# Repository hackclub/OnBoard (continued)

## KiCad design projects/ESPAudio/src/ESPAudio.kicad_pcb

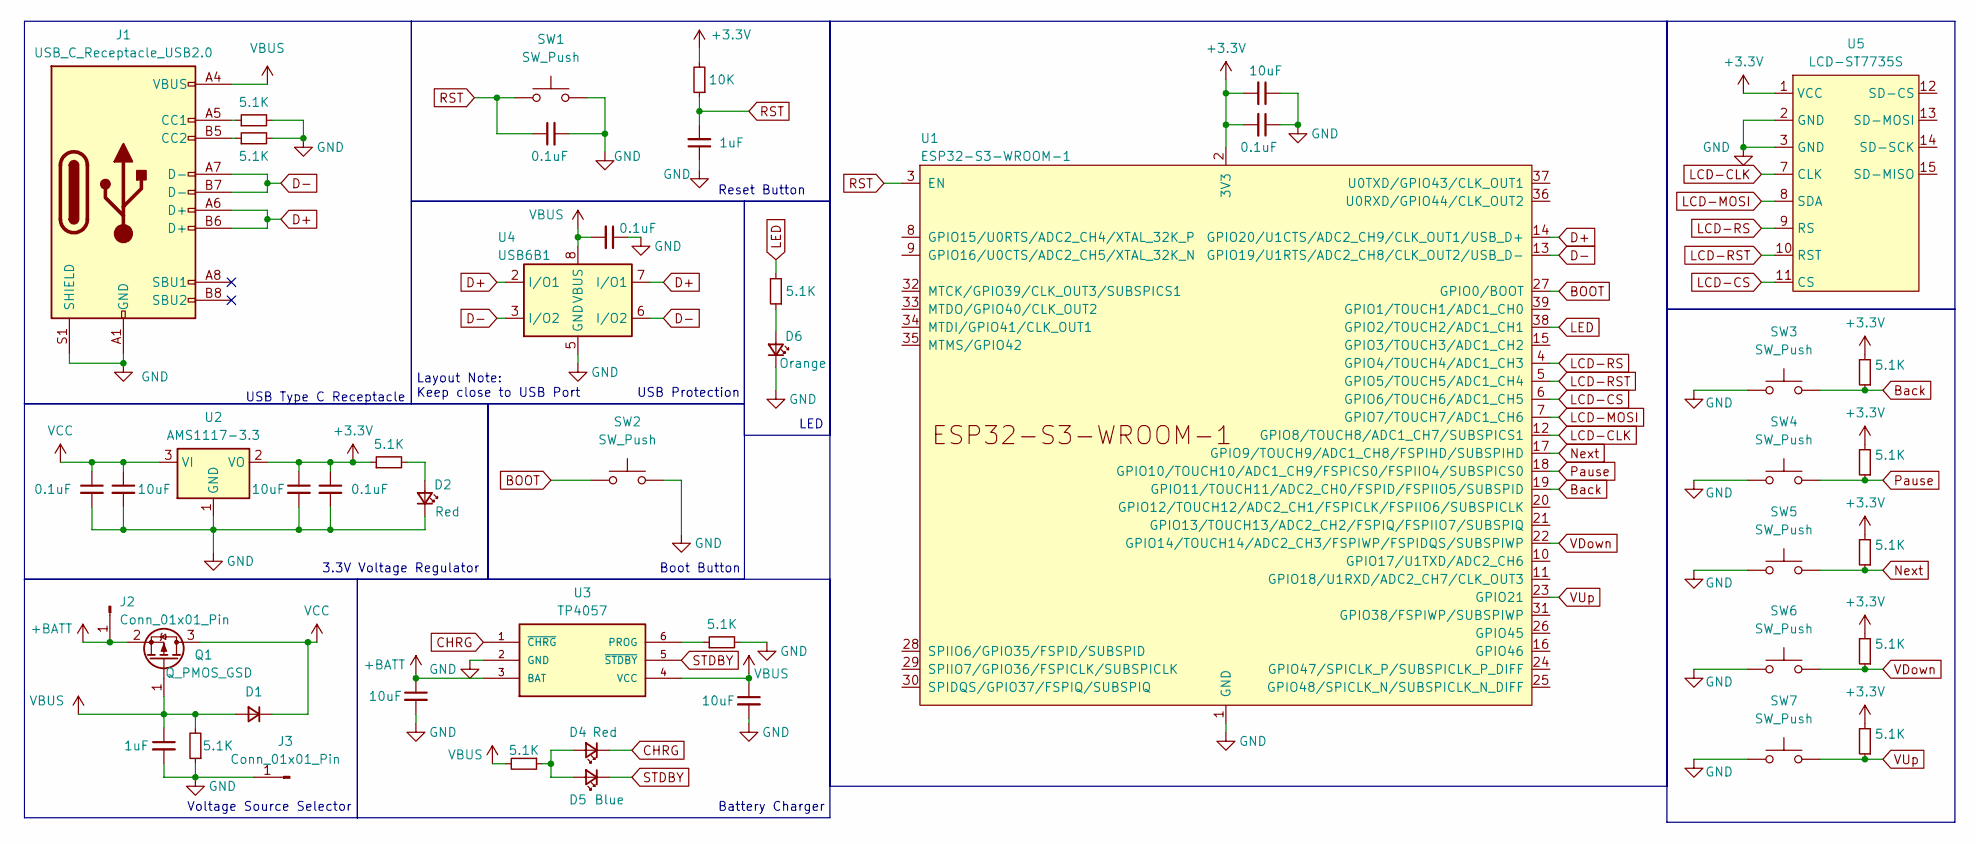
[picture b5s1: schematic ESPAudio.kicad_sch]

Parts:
C1, C6, C9, C12, C13: 10uF; C_0805_2012Metric_Pad1.18x1.45mm_HandSolder
C2, C3, C4, C5, C10: 0.1uF; C_0805_2012Metric_Pad1.18x1.45mm_HandSolder
C7, C8: 1uF; C_0805_2012Metric_Pad1.18x1.45mm_HandSolder
D1: D_Small; D_SOD-123
D2, D4: Red; LED_0805_2012Metric_Pad1.15x1.40mm_HandSolder
D5: Blue; LED_0805_2012Metric_Pad1.15x1.40mm_HandSolder
D6: Orange; LED_0805_2012Metric_Pad1.15x1.40mm_HandSolder
J1: USB_C_Receptacle_USB2.0; USB_C_Receptacle_G-Switch_GT-USB-7010ASV
J2, J3: Conn_01x01_Pin; PinHeader_1x01_P2.54mm_Vertical
Q1: Q_PMOS_GSD; SOT-416
R1, R2, R3, R5, R6, R7, R8, R9, R10, R11, R12, R13: 5.1K; R_0805_2012Metric_Pad1.20x1.40mm_HandSolder
R4: 10K; R_0805_2012Metric_Pad1.20x1.40mm_HandSolder
SW1, SW2: SW_Push; SW_SPST_B3U-1000P
SW3, SW4, SW5, SW6, SW7: SW_Push; Panasonic_EVQPUL_EVQPUC
U1: ESP32-S3-WROOM-1
U2: AMS1117-3.3; SOT-223
U3: TP4057; SOT-23-6_Handsoldering
U4: USB6B1; SOIC-8_3.9x4.9mm_P1.27mm
U5: LCD-ST7735S; PinHeader_1x11_P2.54mm_Vertical

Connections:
+3.3V: C5.1, C6.1, C9.2, C10.2, R3.1, R4.2, R9.2, R10.2, R11.2, R12.2, R13.2, U1.2 (3V3), U2.2 (VO), U5.1 (VCC)
+BATT: C12.1, J2.1, Q1.2 (S), U3.3 (BAT)
BOOT: SW2.1, U1.27 (GPIO0/BOOT); also elsewhere on the board
Back: R9.1, SW3.2, U1.19 (GPIO11/TOUCH11/ADC2_CH0/FSPID/FSPIIO5/S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)
CHRG: D4.1 (K), U3.1 (~CHRG)
D+: J1.A6 (D+), J1.B6 (D+), U1.14 (GPIO20/U1CTS/ADC2_CH9/CLK_OUT1/USB_D+), U4.2 (I/O1), U4.7 (I/O1)
D-: J1.A7 (D-), J1.B7 (D-), U1.13 (GPIO19/U1RTS/ADC2_CH8/CLK_OUT2/USB_D-), U4.3 (I/O2), U4.6 (I/O2)
GND: C1.2, C2.2, C3.1, C4.2, C5.2, C6.2, C7.1, C8.2, C9.1, C10.1, C12.2, C13.2, D2.1 (K), D6.1 (K), J1.A1 (GND), J1.A12 (GND), J1.B1 (GND), J1.B12 (GND), J1.S1 (SHIELD), J3.1, R1.2, R2.2, R6.1, R7.2, SW1.2, SW2.2, SW3.1, SW4.1, SW5.1, SW6.1, SW7.1, U1.1 (GND), U1.40 (GND), U1.41 (GND), U2.1 (GND), U3.2 (GND), U4.4 (GND), U4.5 (GND), U5.2 (GND), U5.3 (GND); also elsewhere on the board
LCD-CLK: U1.12 (GPIO8/TOUCH8/ADC1_CH7/SUBSPICS1), U5.7 (CLK)
LCD-CS: U1.6 (GPIO6/TOUCH6/ADC1_CH5), U5.11 (CS)
LCD-MOSI: U1.7 (GPIO7/TOUCH7/ADC1_CH6), U5.8 (SDA)
LCD-RS: U1.4 (GPIO4/TOUCH4/ADC1_CH3), U5.9 (RS)
LCD-RST: U1.5 (GPIO5/TOUCH5/ADC1_CH4), U5.10 (RST)
LED: R5.2, U1.38 (GPIO2/TOUCH2/ADC1_CH1)
unnamed: D2.2 (A), R3.2
unnamed: D4.2 (A), D5.2 (A), R8.1
unnamed: D6.2 (A), R5.1
unnamed: J1.A5 (CC1), R1.1
unnamed: J1.B5 (CC2), R2.1
unnamed: R7.1, U3.6 (PROG)
Next: R11.1, SW5.2, U1.17 (GPIO9/TOUCH9/ADC1_CH8/FSPIHD/SUBSPIHD)
Pause: R10.1, SW4.2, U1.18 (GPIO10/TOUCH10/ADC1_CH9/FSPICS0/FSPIIO4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)
RST: C4.1, C7.2, R4.1, SW1.1, U1.3 (EN); also elsewhere on the board
STDBY: D5.1 (K), U3.5 (~STDBY)
VBUS: C3.2, C8.1, C13.1, D1.2 (A), J1.A4 (VBUS), J1.A9 (VBUS), J1.B4 (VBUS), J1.B9 (VBUS), Q1.1 (G), R6.2, R8.2, U3.4 (VCC), U4.1 (VBUS), U4.8 (VBUS)
VCC: C1.1, C2.1, D1.1 (K), Q1.3 (D), U2.3 (VI)
VDown: R12.1, SW6.2, U1.22 (GPIO14/TOUCH14/ADC2_CH3/FSPIWP/FSPIDQS/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)
VUp: R13.1, SW7.2, U1.23 (GPIO21)

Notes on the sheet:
LED
Boot Button
Voltage Source Selector
3.3V Voltage Regulator
USB Type C Receptacle
USB Protection
Battery Charger
Layout Note: Keep close to USB Port
Reset Button

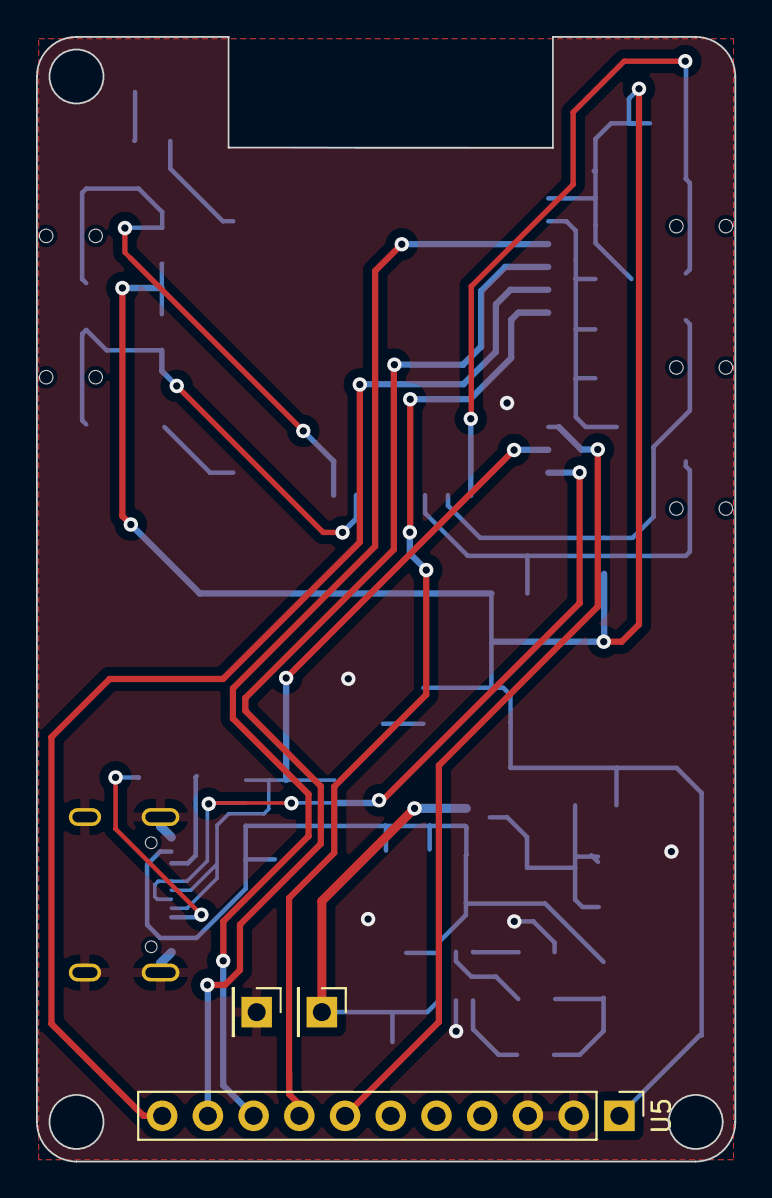
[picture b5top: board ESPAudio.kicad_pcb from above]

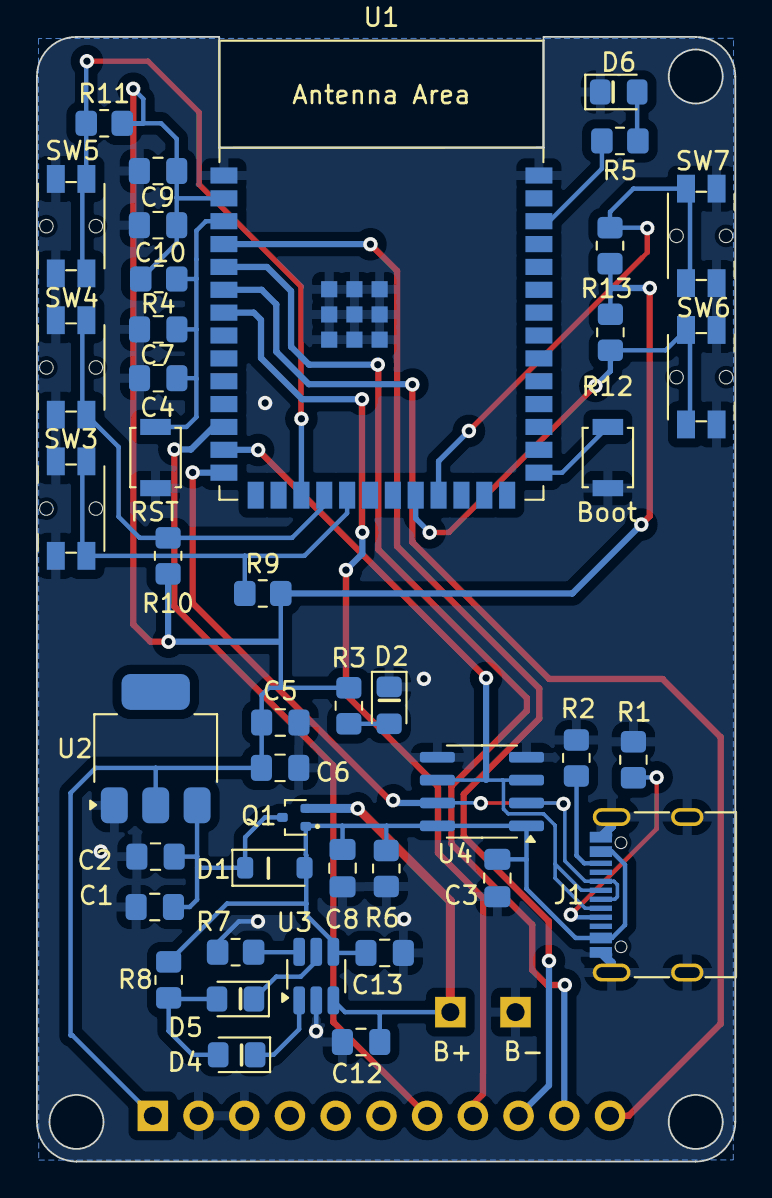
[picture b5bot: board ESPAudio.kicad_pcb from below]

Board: 2 copper layers, 38.8 x 62.5 mm, 46 parts (43 on the bottom side), 28 nets.

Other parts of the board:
Boot: SW_Push; SW_SPST_B3U-1000P
RST: SW_Push; SW_SPST_B3U-1000P

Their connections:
BOOT: Boot.1; also elsewhere on the board
GND: Boot.2, RST.2; also elsewhere on the board
RST: RST.1; also elsewhere on the board

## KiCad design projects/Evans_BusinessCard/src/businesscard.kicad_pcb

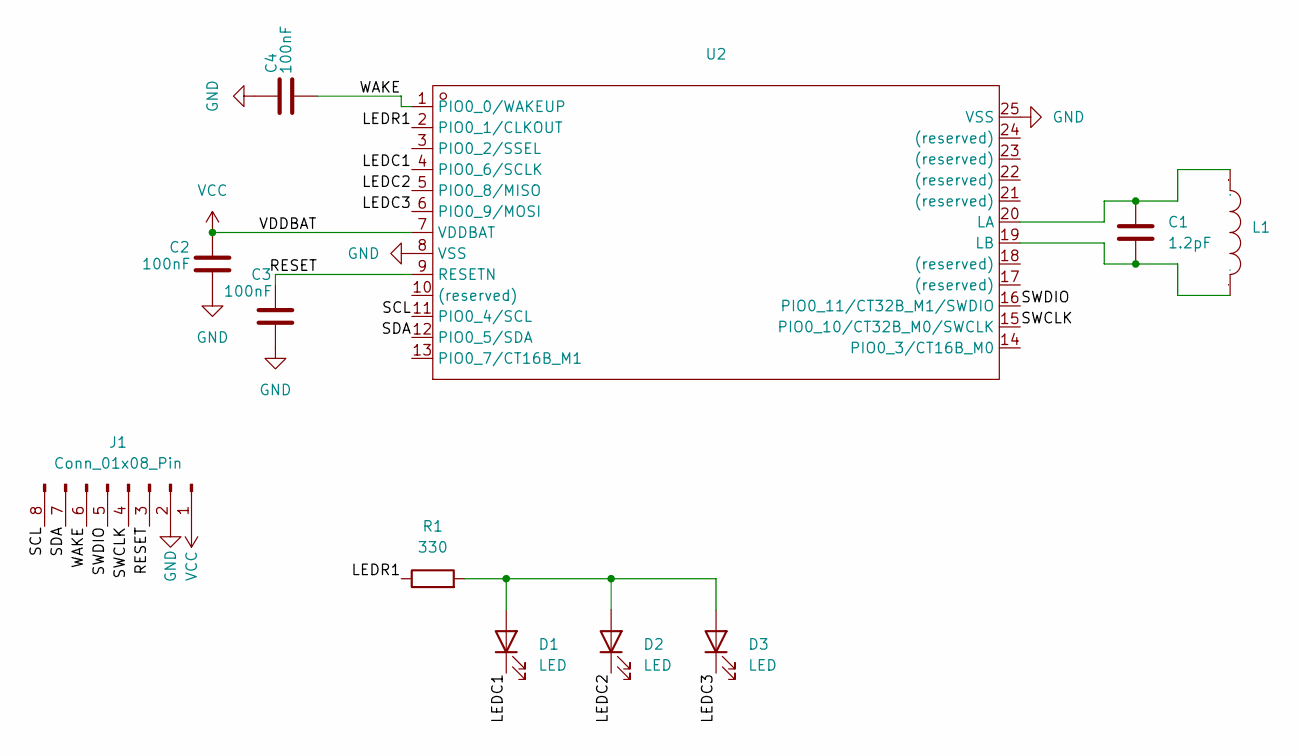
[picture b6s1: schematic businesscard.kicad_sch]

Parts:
C1: 1.2pF; C_0201_0603Metric
C2, C3, C4: 100nF; C_0201_0603Metric
D1, D2, D3: LED; LED_0805_2012Metric
J1: Conn_01x08_Pin; 8-Pin-Pads
L1: 25X48MM_NFC_EXPOSED_ANTENNA
R1: 330; R_0201_0603Metric
U2: NXP LPC8N04FHI24E; Manufacturer Part LPC8N04FHI24E; LCSC Part Name LPC8N04FHI24E

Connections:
/LEDC1: D1.1 (K), U2.4 (PIO0_6/SCLK)
/LEDC2: D2.1 (K), U2.5 (PIO0_8/MISO)
/LEDC3: D3.1 (K), U2.6 (PIO0_9/MOSI)
/LEDR1: R1.1, U2.2 (PIO0_1/CLKOUT)
/RESET: C3.1, J1.3, U2.9 (RESETN)
/SCL: J1.8, U2.11 (PIO0_4/SCL)
/SDA: J1.7, U2.12 (PIO0_5/SDA)
/SWCLK: J1.4, U2.15 (PIO0_10/CT32B_M0/SWCLK)
/SWDIO: J1.5, U2.16 (PIO0_11/CT32B_M1/SWDIO)
/WAKE: C4.1, J1.6, U2.1 (PIO0_0/WAKEUP)
GND: C2.2, C3.2, C4.2, J1.2, U2.8 (VSS), U2.25 (VSS)
unnamed: D1.2 (A), D2.2 (A), D3.2 (A), R1.2
unnamed: C1.1, L1.1, U2.20 (LA)
unnamed: C1.2, L1.2, U2.19 (LB)
VCC: C2.1, J1.1, U2.7 (VDDBAT)

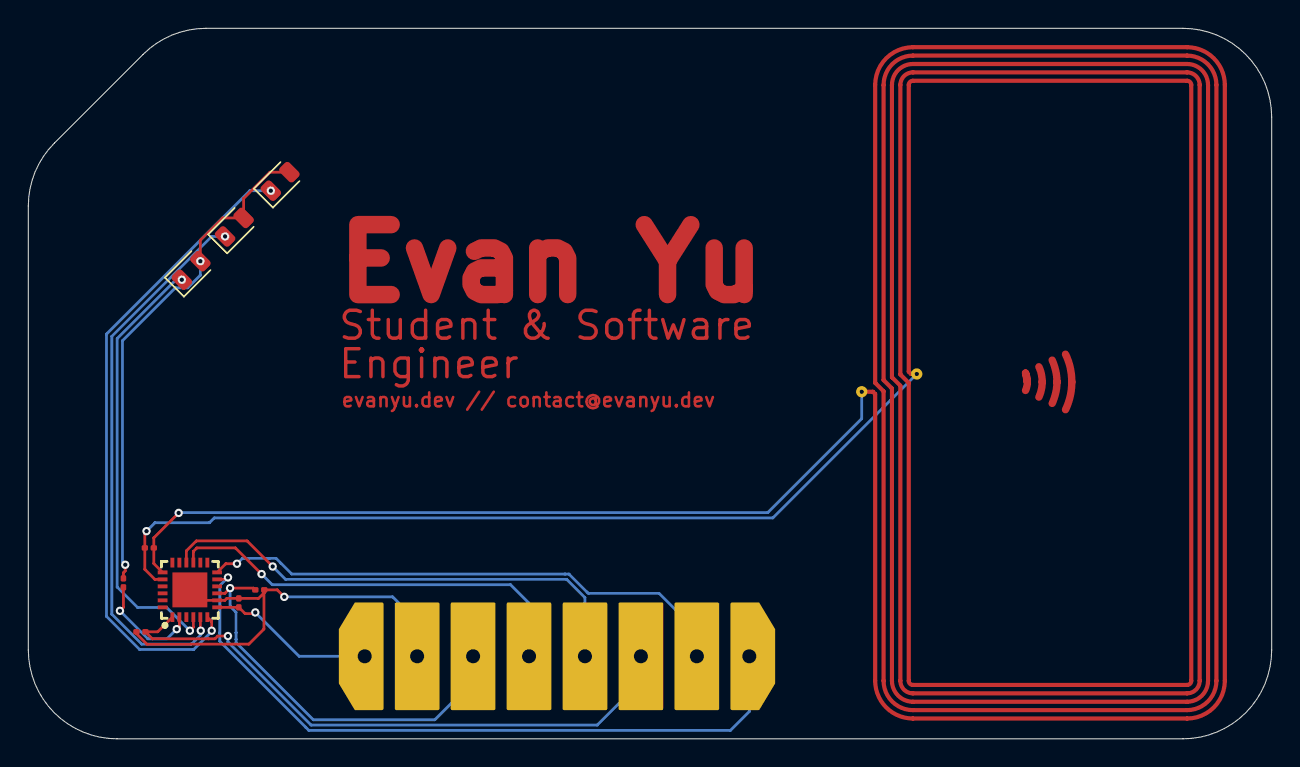
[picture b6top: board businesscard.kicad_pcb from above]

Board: 2 copper layers, 88.9 x 50.8 mm, 11 parts (0 on the bottom side), 15 nets.

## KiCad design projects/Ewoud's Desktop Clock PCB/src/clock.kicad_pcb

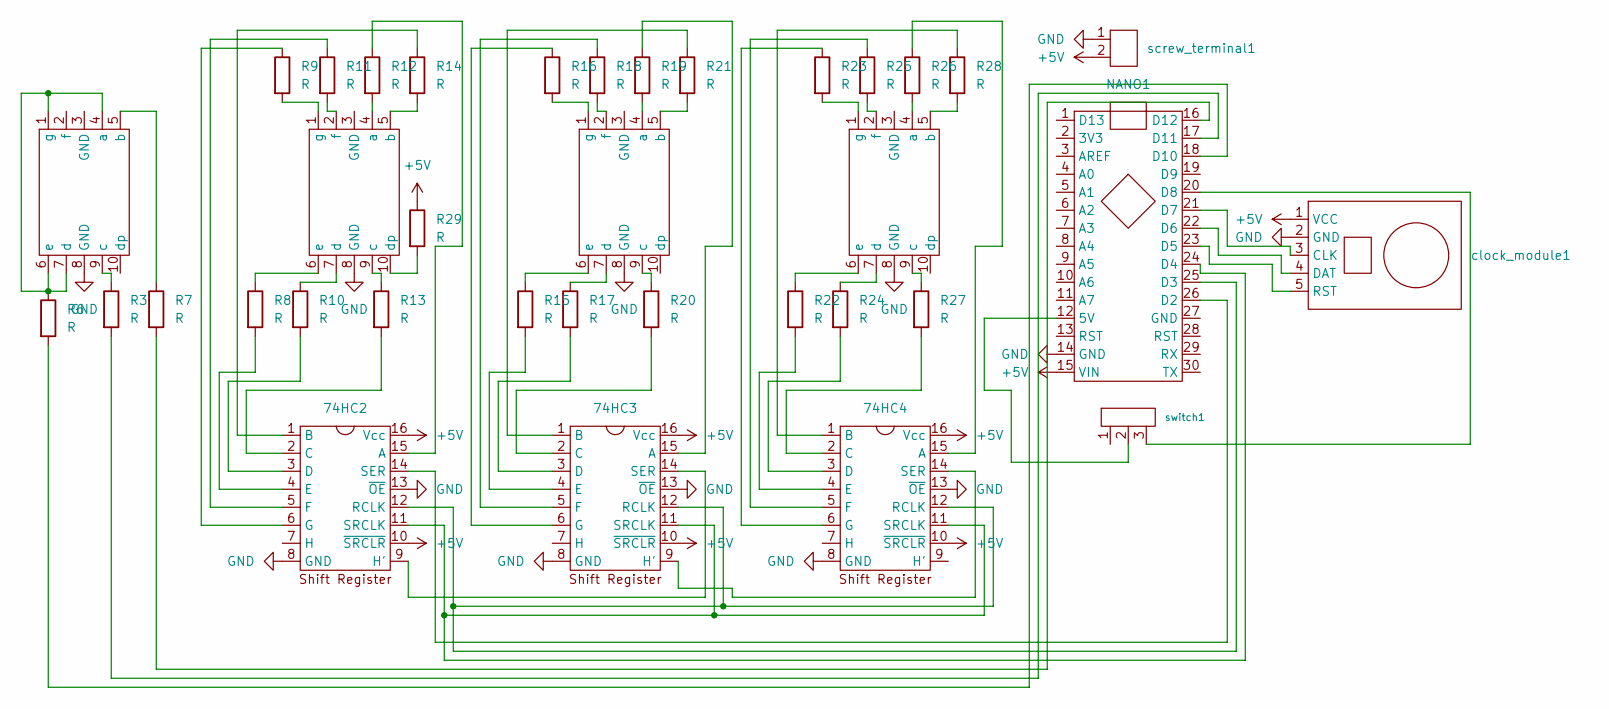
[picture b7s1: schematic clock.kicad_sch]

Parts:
8seg_display1, 8seg_display2, 8seg_display3, 8seg_display4: 8seg_display
74HC2, 74HC3, 74HC4: SN74HC595N - PDIP
NANO1: nano
R3, R6, R7, R8, R9, R10, R11, R12, R13, R14, R15, R16, R17, R18, R19, R20, R21, R22, R23, R24, R25, R26, R27, R28, R29: R
clock_module1: clock_module
screw_terminal1: screw_terminal
switch1: switch

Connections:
+5V: 74HC2.10 (~SRCLR), 74HC2.16 (Vcc), 74HC3.10 (~SRCLR), 74HC3.16 (Vcc), 74HC4.10 (~SRCLR), 74HC4.16 (Vcc), NANO1.15 (VIN), R29.1, clock_module1.1 (VCC), screw_terminal1.2; also elsewhere on the board
GND: 8seg_display1.8 (GND), 8seg_display2.8 (GND), 8seg_display3.8 (GND), 8seg_display4.8 (GND), 74HC2.8 (GND), 74HC2.13 (~OE), 74HC3.8 (GND), 74HC3.13 (~OE), 74HC4.8 (GND), 74HC4.13 (~OE), NANO1.14 (GND), clock_module1.2 (GND), screw_terminal1.1; also elsewhere on the board
unnamed: 8seg_display1.1 (g), 8seg_display1.4 (a), 8seg_display1.6 (e), 8seg_display1.7 (d), R6.1
unnamed: 8seg_display1.5 (b), R7.1
unnamed: 8seg_display1.9 (c), R3.1
unnamed: 8seg_display2.4 (a), R12.2
unnamed: 8seg_display2.5 (b), R14.2
unnamed: 8seg_display2.9 (c), R13.1
unnamed: 8seg_display2.7 (d), R10.1
unnamed: 8seg_display2.10 (dp), R29.2
unnamed: 8seg_display2.6 (e), R8.1
unnamed: 8seg_display2.2 (f), R11.2
unnamed: 8seg_display2.1 (g), R9.2
unnamed: 8seg_display3.4 (a), R19.2
unnamed: 8seg_display3.5 (b), R21.2
unnamed: 8seg_display3.9 (c), R20.1
unnamed: 8seg_display3.7 (d), R17.1
unnamed: 8seg_display3.6 (e), R15.1
unnamed: 8seg_display3.2 (f), R18.2
unnamed: 8seg_display3.1 (g), R16.2
unnamed: 8seg_display4.4 (a), R26.2
unnamed: 8seg_display4.5 (b), R28.2
unnamed: 8seg_display4.9 (c), R27.1
unnamed: 8seg_display4.7 (d), R24.1
unnamed: 8seg_display4.6 (e), R22.1
unnamed: 8seg_display4.2 (f), R25.2
unnamed: 8seg_display4.1 (g), R23.2
unnamed 27: 74HC2.15 (A), R12.1; also elsewhere on the board
unnamed 28: 74HC2.1 (B), R14.1; also elsewhere on the board
unnamed 29: 74HC2.2 (C), R13.2; also elsewhere on the board
unnamed 30: 74HC2.3 (D), R10.2; also elsewhere on the board
unnamed 31: 74HC2.4 (E), R8.2; also elsewhere on the board
unnamed 32: 74HC2.5 (F), R11.1; also elsewhere on the board
unnamed 33: 74HC2.6 (G), R9.1; also elsewhere on the board
unnamed 34: 74HC2.9 (H'), 74HC3.14 (SER); also elsewhere on the board
unnamed 35: 74HC2.12 (RCLK), 74HC3.12 (RCLK), 74HC4.12 (RCLK), NANO1.25 (D3); also elsewhere on the board
unnamed 36: 74HC2.14 (SER), NANO1.26 (D2); also elsewhere on the board
unnamed 37: 74HC2.11 (SRCLK), 74HC3.11 (SRCLK), 74HC4.11 (SRCLK), NANO1.24 (D4); also elsewhere on the board
unnamed: 74HC3.15 (A), R19.1
unnamed: 74HC3.1 (B), R21.1
unnamed: 74HC3.2 (C), R20.2
unnamed: 74HC3.3 (D), R17.2
unnamed: 74HC3.4 (E), R15.2
unnamed: 74HC3.5 (F), R18.1
unnamed: 74HC3.6 (G), R16.1
unnamed: 74HC3.9 (H'), 74HC4.14 (SER)
unnamed: 74HC4.15 (A), R26.1
unnamed: 74HC4.1 (B), R28.1
unnamed: 74HC4.2 (C), R27.2
unnamed: 74HC4.3 (D), R24.2
unnamed: 74HC4.4 (E), R22.2
unnamed: 74HC4.5 (F), R25.1
unnamed: 74HC4.6 (G), R23.1
unnamed: NANO1.12 (5V), switch1.2
unnamed: NANO1.23 (D5), clock_module1.5 (RST)
unnamed: NANO1.22 (D6), clock_module1.4 (DAT)
unnamed: NANO1.21 (D7), clock_module1.3 (CLK)
unnamed: NANO1.20 (D8), switch1.3
unnamed: NANO1.18 (D10), R6.2
unnamed: NANO1.17 (D11), R3.2
unnamed: NANO1.16 (D12), R7.2

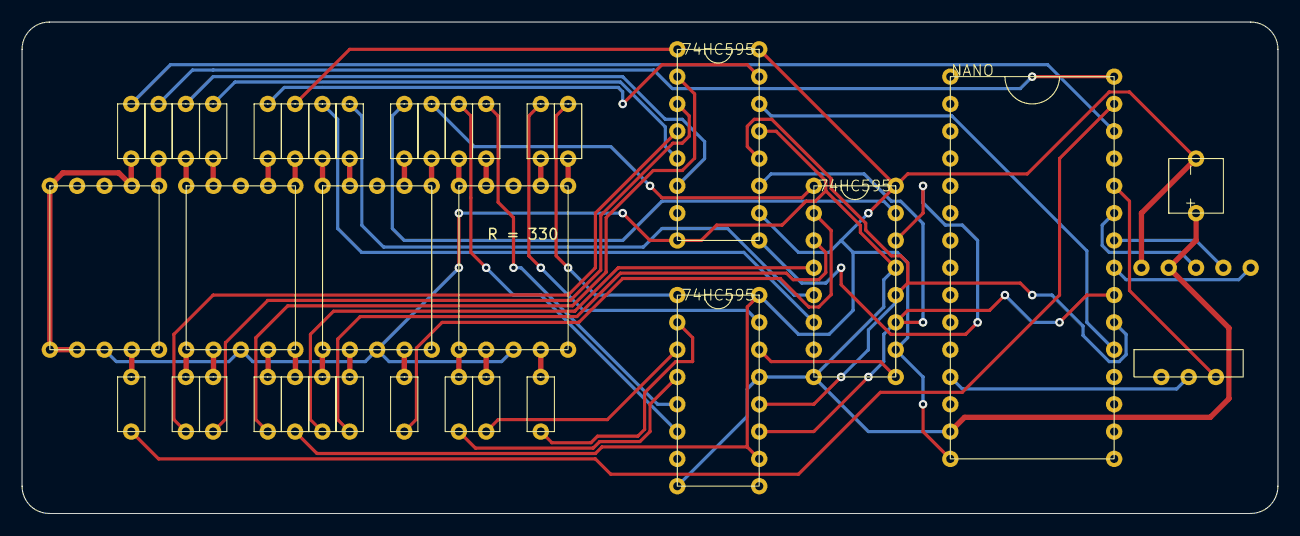
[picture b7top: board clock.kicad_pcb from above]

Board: 2 copper layers, 116.8 x 45.7 mm, 36 parts (0 on the bottom side), 61 nets.

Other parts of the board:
74HC595: SN74HC595N - PDIP

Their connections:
+5V: 74HC595.10 (~SRCLR), 74HC595.16 (Vcc); also elsewhere on the board
GND: 74HC595.8 (GND), 74HC595.13 (~OE); also elsewhere on the board
unnamed 27: 74HC595.15 (A); also elsewhere on the board
unnamed 28: 74HC595.1 (B); also elsewhere on the board
unnamed 29: 74HC595.2 (C); also elsewhere on the board
unnamed 30: 74HC595.3 (D); also elsewhere on the board
unnamed 31: 74HC595.4 (E); also elsewhere on the board
unnamed 32: 74HC595.5 (F); also elsewhere on the board
unnamed 33: 74HC595.6 (G); also elsewhere on the board
unnamed 34: 74HC595.9 (H'); also elsewhere on the board
unnamed 35: 74HC595.12 (RCLK); also elsewhere on the board
unnamed 36: 74HC595.14 (SER); also elsewhere on the board
unnamed 37: 74HC595.11 (SRCLK); also elsewhere on the board
